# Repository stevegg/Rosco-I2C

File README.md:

# Rosco-I2C
I2C Interface expansion for Rosco-m68k

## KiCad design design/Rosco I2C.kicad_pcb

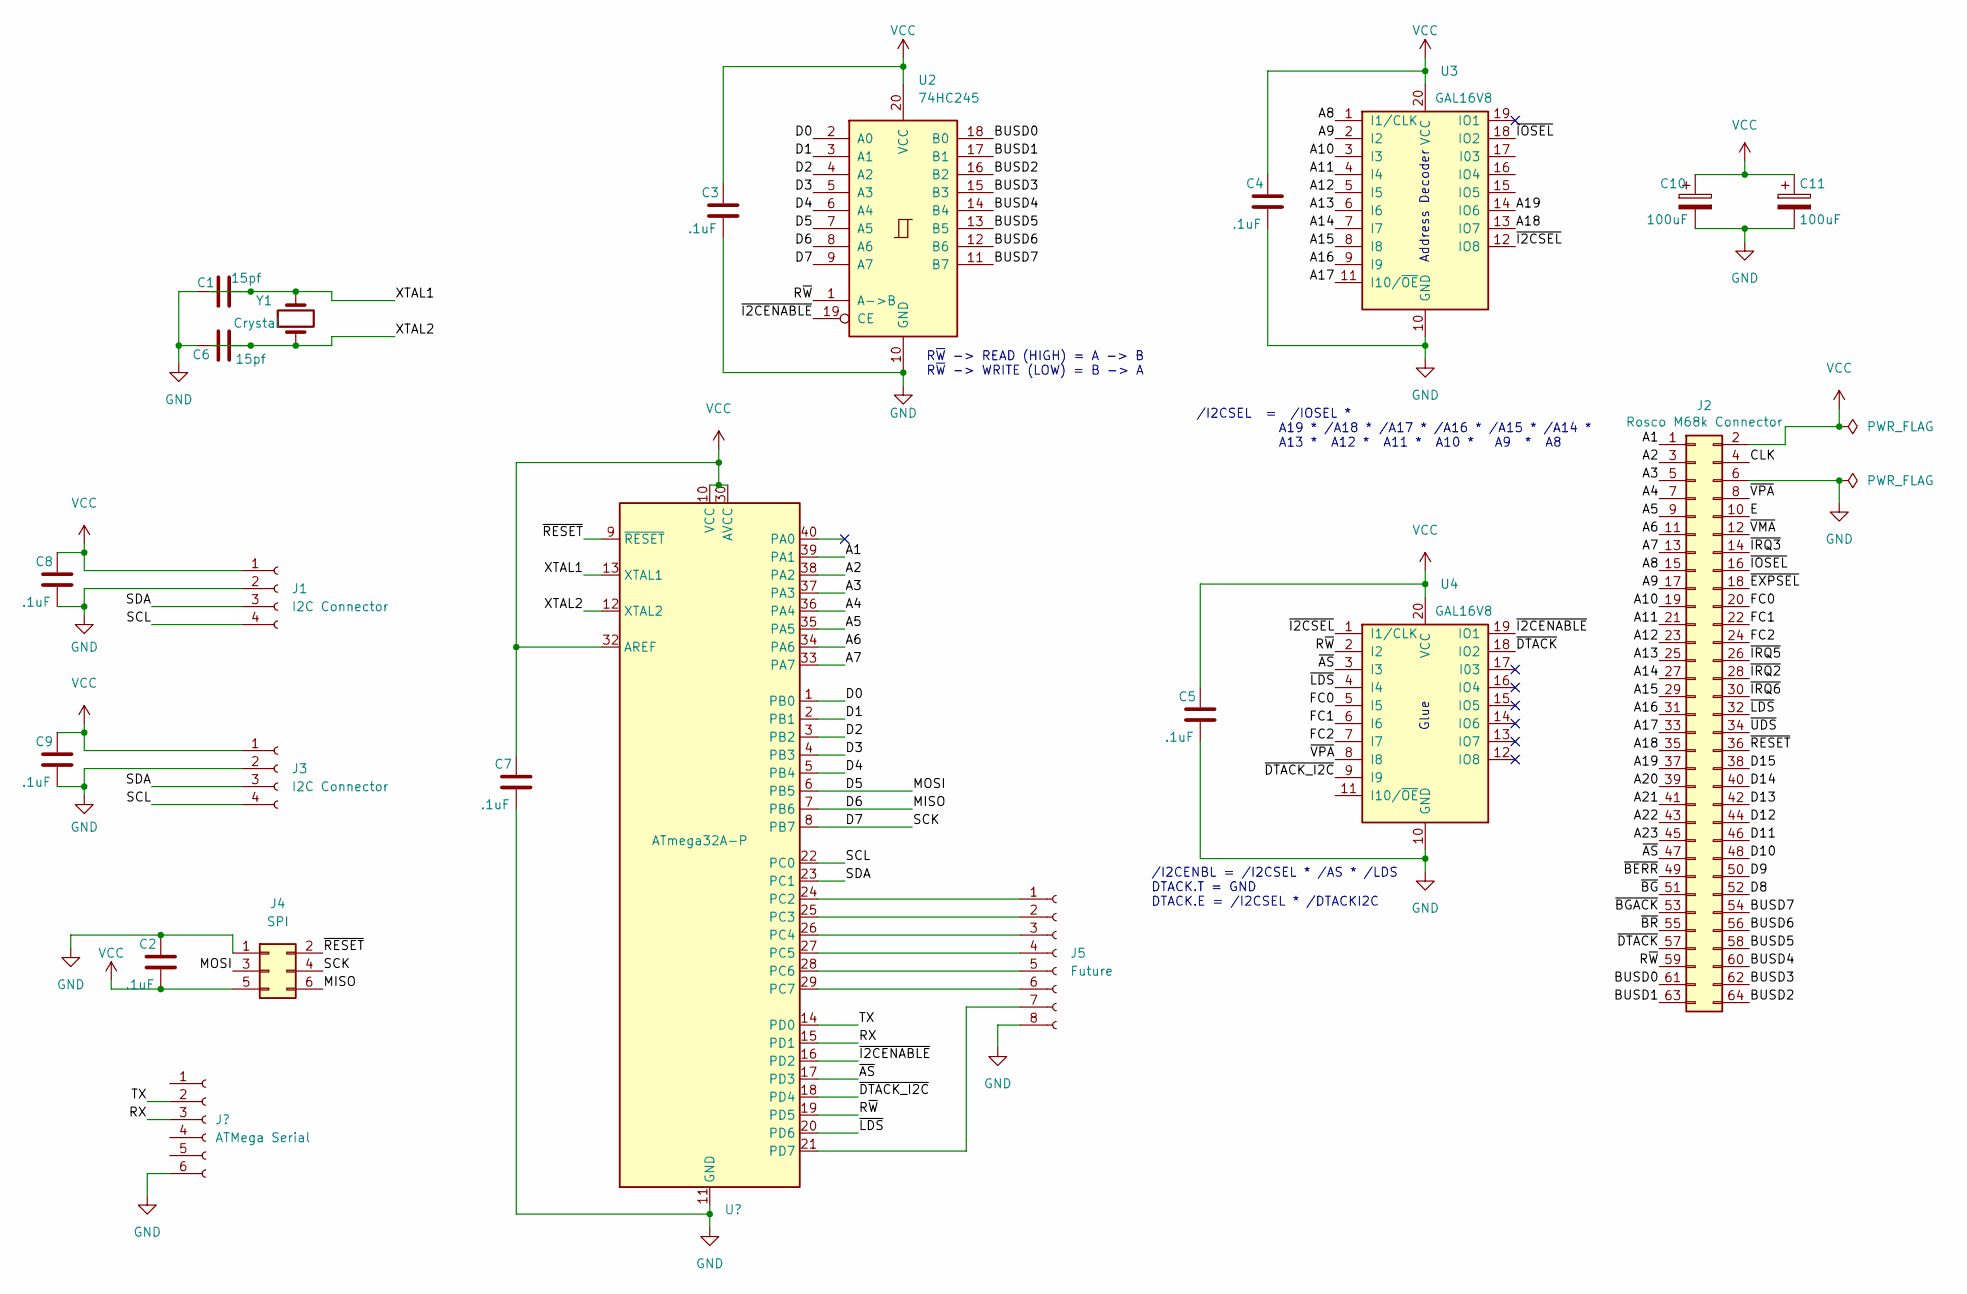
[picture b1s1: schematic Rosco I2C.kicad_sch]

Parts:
C1, C6: 15pf; C_Rect_L4.0mm_W2.5mm_P2.50mm
C2, C3, C4, C5, C7, C8, C9: .1uF; C_Rect_L4.0mm_W2.5mm_P2.50mm
C10, C11: 100uF; CP_Radial_D5.0mm_P2.50mm
J1, J3: I2C Connector; PinHeader_1x04_P2.54mm_Vertical
J2: Rosco M68k Connector; PinHeader_2x32_P2.54mm_Vertical
J4: SPI; PinHeader_2x03_P2.54mm_Vertical
J5: Future; PinSocket_1x08_P2.54mm_Vertical
U2: 74HC245; DIP-20_W7.62mm_Socket_LongPads
U3, U4: GAL16V8; DIP-20_W7.62mm_Socket_LongPads
Y1: Crystal; Crystal_HC49-4H_Vertical

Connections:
/A1: J2.1; also elsewhere on the board
/A2: J2.3; also elsewhere on the board
/A3: J2.5; also elsewhere on the board
/A4: J2.7; also elsewhere on the board
/A5: J2.9; also elsewhere on the board
/A6: J2.11; also elsewhere on the board
/A7: J2.13; also elsewhere on the board
/A8: J2.15, U3.1 (I1/CLK)
/A9: J2.17, U3.2 (I2)
/A10: J2.19, U3.3 (I3)
/A11: J2.21, U3.4 (I4)
/A12: J2.23, U3.5 (I5)
/A13: J2.25, U3.6 (I6)
/A14: J2.27, U3.7 (I7)
/A15: J2.29, U3.8 (I8)
/A16: J2.31, U3.9 (I9)
/A17: J2.33, U3.11 (I10/~OE)
/A18: J2.35, U3.13 (IO7)
/A19: J2.37, U3.14 (IO6)
/A20: J2.39, U3.15 (IO5)
/A21: J2.41, U3.16 (IO4)
/A22: J2.43, U3.17 (I03)
/BUSD0: J2.61, U2.18 (B0)
/BUSD1: J2.63, U2.17 (B1)
/BUSD2: J2.64, U2.16 (B2)
/BUSD3: J2.62, U2.15 (B3)
/BUSD4: J2.60, U2.14 (B4)
/BUSD5: J2.58, U2.13 (B5)
/BUSD6: J2.56, U2.12 (B6)
/BUSD7: J2.54, U2.11 (B7)
/CLK: J2.4
/D0: U2.2 (A0); also elsewhere on the board
/D1: U2.3 (A1); also elsewhere on the board
/D2: U2.4 (A2); also elsewhere on the board
/D3: U2.5 (A3); also elsewhere on the board
/D4: U2.6 (A4); also elsewhere on the board
/D5: J4.3, U2.7 (A5); also elsewhere on the board
/D6: J4.6, U2.8 (A6); also elsewhere on the board
/D7: J4.4, U2.9 (A7); also elsewhere on the board
/D8: J2.52
/D9: J2.50
/D10: J2.48
/D11: J2.46
/D12: J2.44
/D13: J2.42
/D14: J2.40
/D15: J2.38
/E: J2.10
/FC0: J2.20, U4.5 (I5)
/FC1: J2.22, U4.6 (I6)
/FC2: J2.24, U4.7 (I7)
/R~W: J2.59, U2.1 (A->B), U4.2 (I2); also elsewhere on the board
/SCL: J1.4, J3.4; also elsewhere on the board
/SDA: J1.3, J3.3; also elsewhere on the board
/XTAL1: C1.2, Y1.2; also elsewhere on the board
/XTAL2: C6.2, Y1.1; also elsewhere on the board
/~AS: J2.47, U4.3 (I3); also elsewhere on the board
/~BERR: J2.49
/~BGACK: J2.53
/~BG: J2.51
/~BR: J2.55
/~DTACK: J2.57, U4.18 (IO2); also elsewhere on the board
/~EXPSEL: J2.18
/~I2CENABLE: U2.19 (CE), U4.19 (IO1); also elsewhere on the board
/~I2CSEL: U3.12 (IO8), U4.1 (I1/CLK)
/~IRQ2: J2.28
/~IRQ3: J2.14
/~IRQ5: J2.26
/~IRQ6: J2.30
/~LDS: J2.32, U4.4 (I4); also elsewhere on the board
/~RESET: J2.36, J4.2; also elsewhere on the board
/~UDS: J2.34
/~VMA: J2.12
/~VPA: J2.8, U4.8 (I8)
GND: C1.1, C2.1, C3.2, C4.2, C5.2, C6.1, C7.2, C8.2, C9.2, C10.2, C11.2, J1.2, J2.6, J3.2, J4.1, U2.10 (GND), U3.10 (GND), U4.10 (GND); also elsewhere on the board
unnamed 75: J5.1; also elsewhere on the board
unnamed 76: J5.2; also elsewhere on the board
unnamed 77: J5.3; also elsewhere on the board
unnamed 78: J5.4; also elsewhere on the board
unnamed 79: J5.5; also elsewhere on the board
unnamed 80: J5.6; also elsewhere on the board
unnamed 81: J5.7; also elsewhere on the board
unnamed 82: J5.8; also elsewhere on the board
VCC: C2.2, C3.1, C4.1, C5.1, C7.1, C8.1, C9.1, C10.1, C11.1, J1.1, J2.2, J3.1, J4.5, U2.20 (VCC), U3.20 (VCC), U4.20 (VCC); also elsewhere on the board

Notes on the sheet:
R~{W} -> READ (HIGH) = A -> B R~{W} -> WRITE (LOW) = B -> A
/I2CSEL = /IOSEL * A19 * /A18 * /A17 * /A16 * /A15 * /A14 * A13 * A12 * A11 * A10 * A9 * A8
Glue
Address Decoder
/I2CENBL = /I2CSEL * /AS * /LDS DTACK.T = GND DTACK.E = /I2CSEL * /DTACKI2C

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
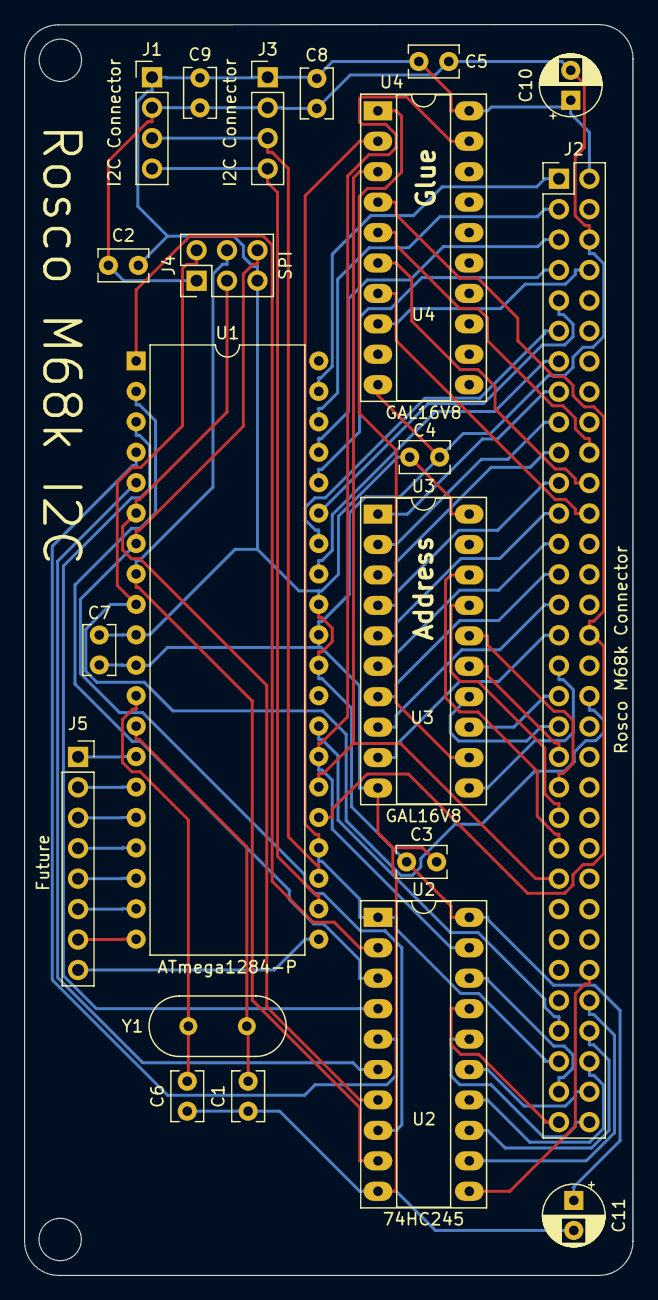
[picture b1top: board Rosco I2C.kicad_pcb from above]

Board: 2 copper layers, 50.8 x 104.4 mm, 21 parts (0 on the bottom side), 64 nets.

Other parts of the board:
U1: ATmega1284-P; DIP-40_W15.24mm

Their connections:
/A1: U1.39 (PA1); also elsewhere on the board
/A2: U1.38 (PA2); also elsewhere on the board
/A3: U1.37 (PA3); also elsewhere on the board
/A4: U1.36 (PA4); also elsewhere on the board
/A5: U1.35 (PA5); also elsewhere on the board
/A6: U1.34 (PA6); also elsewhere on the board
/A7: U1.33 (PA7); also elsewhere on the board
/D0: U1.1 (PB0); also elsewhere on the board
/D1: U1.2 (PB1); also elsewhere on the board
/D2: U1.3 (PB2); also elsewhere on the board
/D3: U1.4 (PB3); also elsewhere on the board
/D4: U1.5 (PB4); also elsewhere on the board
/D5: U1.6 (PB5); also elsewhere on the board
/D6: U1.7 (PB6); also elsewhere on the board
/D7: U1.8 (PB7); also elsewhere on the board
/R~W: U1.24 (PC2); also elsewhere on the board
/SCL: U1.22 (PC0); also elsewhere on the board
/SDA: U1.23 (PC1); also elsewhere on the board
/XTAL1: U1.13 (XTAL1); also elsewhere on the board
/XTAL2: U1.12 (XTAL2); also elsewhere on the board
/~AS: U1.26 (PC4); also elsewhere on the board
/~DTACK: U1.28 (PC6); also elsewhere on the board
/~I2CENABLE: U1.27 (PC5); also elsewhere on the board
/~LDS: U1.25 (PC3); also elsewhere on the board
/~RESET: U1.9 (~RESET); also elsewhere on the board
GND: U1.11 (GND), U1.31 (GND); also elsewhere on the board
unnamed 75: U1.14 (PD0); also elsewhere on the board
unnamed 76: U1.15 (PD1); also elsewhere on the board
unnamed 77: U1.16 (PD2); also elsewhere on the board
unnamed 78: U1.17 (PD3); also elsewhere on the board
unnamed 79: U1.18 (PD4); also elsewhere on the board
unnamed 80: U1.19 (PD5); also elsewhere on the board
unnamed 81: U1.20 (PD6); also elsewhere on the board
unnamed 82: U1.21 (PD7); also elsewhere on the board
VCC: U1.10 (VCC), U1.30 (AVCC), U1.32 (AREF); also elsewhere on the board

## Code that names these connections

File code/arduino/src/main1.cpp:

// #include <Arduino.h>
// #include <Adafruit_GFX.h>
// #include <Adafruit_LEDBackpack.h>

// /**
//  * Notes:
//  * 
//  * Port Manipulation
//  *    DDR 1 = OUTPUT, 0 = INPUT
//  *    Use PIN to read
//  *    Use PORT to write
//  */

// Adafruit_7segment matrix = Adafruit_7segment();

// #define DTACK_ARDUINO_PIN 15
// #define DTACK_DDR DDRD
// #define DTACK_PIN PIND7
// #define DTACK_PORT PORTD

// #define I2CENABLE_ARDUINO_PIN 11
// #define I2CENABLE_DDR DDRD
// #define I2CENABLE_PIN PIND3
// #define I2CENABLE_PINS PIND
// #define I2CENABLE_PORT PORTD
// #define I2CENABLE_INTERRUPT PCINT27

// #define AS_ARDUINO_PIN  10
// #define AS_DDR          DDRD
// #define AS_PIN          PIND2
// #define AS_PORT         PORTD

// #define RW_ARDUINO_PIN  13
// #define RW_DDR          DDRD
// #define RW_PIN          PIND5
// #define RW_PORT         PORTD

// #define LDS_ARDUINO_PIN 14
// #define LDS_DDR         DDRD
// #define LDS_PIN         PIND6
// #define LDS_PORT        PORTD

// #define DATA_PORT       PORTA
// #define DATA_DDR        DDRA
// #define DATA_PIN        PINA

// #define ADDRESS_PORT    PORTB
// #define ADDRESS_PIN     PINB
// #define ADDRESS_DDR     DDRB

// // ISR (INT1_vect) {
// //   // Assert DTACK signal LOW
// //   DTACK_PORT &= ~(1<<DTACK_PIN);
// //   DTACK_DDR |= (1<<DTACK_PIN);
// //   // Read data, address and RW ports/pins
// //   gvData = DATA_PIN;
// //   gvAddress = ADDRESS_PIN;
// //   DTACK_DDR &= ~(1<<DTACK_PIN);
// //   DTACK_PORT |= (1<<DTACK_PIN);
// //   gvRW = (RW_PORT & (1<<RW_PIN));

// //   // Flag to indicate that the bus needs processing
// //   gvProcessBus = true;
// // }

// void setup() {
//   // Setup Address Port as INPUT
//   ADDRESS_DDR = 0x00;
//   // Setup Data Port initially as INPUT
//   DATA_DDR = 0x00;
//   // TriState DTACK using DDR as INPUT to turn it off
//   DTACK_DDR &= ~(1<<DTACK_PIN);
//   // Set hi
//   DTACK_PORT |= (1<<DTACK_PIN);

//   // I2CENABLE is an INPUT
//   I2CENABLE_DDR &= ~(1<<I2CENABLE_PIN);
//   // Pullup
//   PORTD |= (1<<I2CENABLE_PIN);

//   // AS is an INPUT
//   AS_DDR &= ~(1<<AS_PIN);

//   // RW pin is an INPUT
//   RW_DDR &= ~(1<<RW_PIN);

//   // LDS pin is an INPUT
//   LDS_DDR &= ~(1<<LDS_PIN);

//   // cli();
//   // EICRA &= ~(bit(ISC00) | bit (ISC01));  // clear existing flags
//   // EICRA |= bit (ISC01);    // set wanted flags (falling level interrupt)
//   // EIMSK |= bit (INT1);     // enable it
//   // Disable timers
//   TIMSK0 &= ~_BV(TOIE0);
//   // TCCR1A &= ~((1 << CS12) | (1 << CS11) | (1 << CS10));
//   // TCCR1B &= ~((1 << CS12) | (1 << CS11) | (1 << CS10));
//   // sei();
// }

// void loop() {

//   // byte address = 0x00;
//   // byte data = 0x00;
//   // boolean RW = false;

//   if ( !(I2CENABLE_PINS & (1<<I2CENABLE_PIN) ) ) {
//     DTACK_PORT &= ~(1<<DTACK_PIN);
//     DTACK_DDR |= (1<<DTACK_PIN);
//     // Read data, address and RW ports/pins
//     // data = DATA_PIN;
//     // address = ADDRESS_PIN;
//     // RW = (RW_PORT & (1<<RW_PIN));
//     DTACK_DDR &= ~(1<<DTACK_PIN);
//     DTACK_PORT |= (1<<DTACK_PIN);
//   }

//   // // Did an interrupt get triggered?
//   // if ( gvProcessBus ) {
//   //   // Serial.println("processBus...");

//   //   // char buffer[128];

//   //   // sprintf(buffer, "I2C: %c %02X : %02X", (gvRW)?'R':'W', gvAddress, gvData);
//   //   // Serial.println(buffer);

//   //   // if gvRW is false then we've got a write from the processor
//   //   if ( !gvRW ) {
//   //     // Write data to the 7 segment LED
//   //     matrix.print(gvData, HEX);
//   //     matrix.writeDisplay();
//   //   }

//   //   // Finished
//   //   gvProcessBus = false;    
//   // }
// }

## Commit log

2022-10-08 Checkpoint. Working with AVR
